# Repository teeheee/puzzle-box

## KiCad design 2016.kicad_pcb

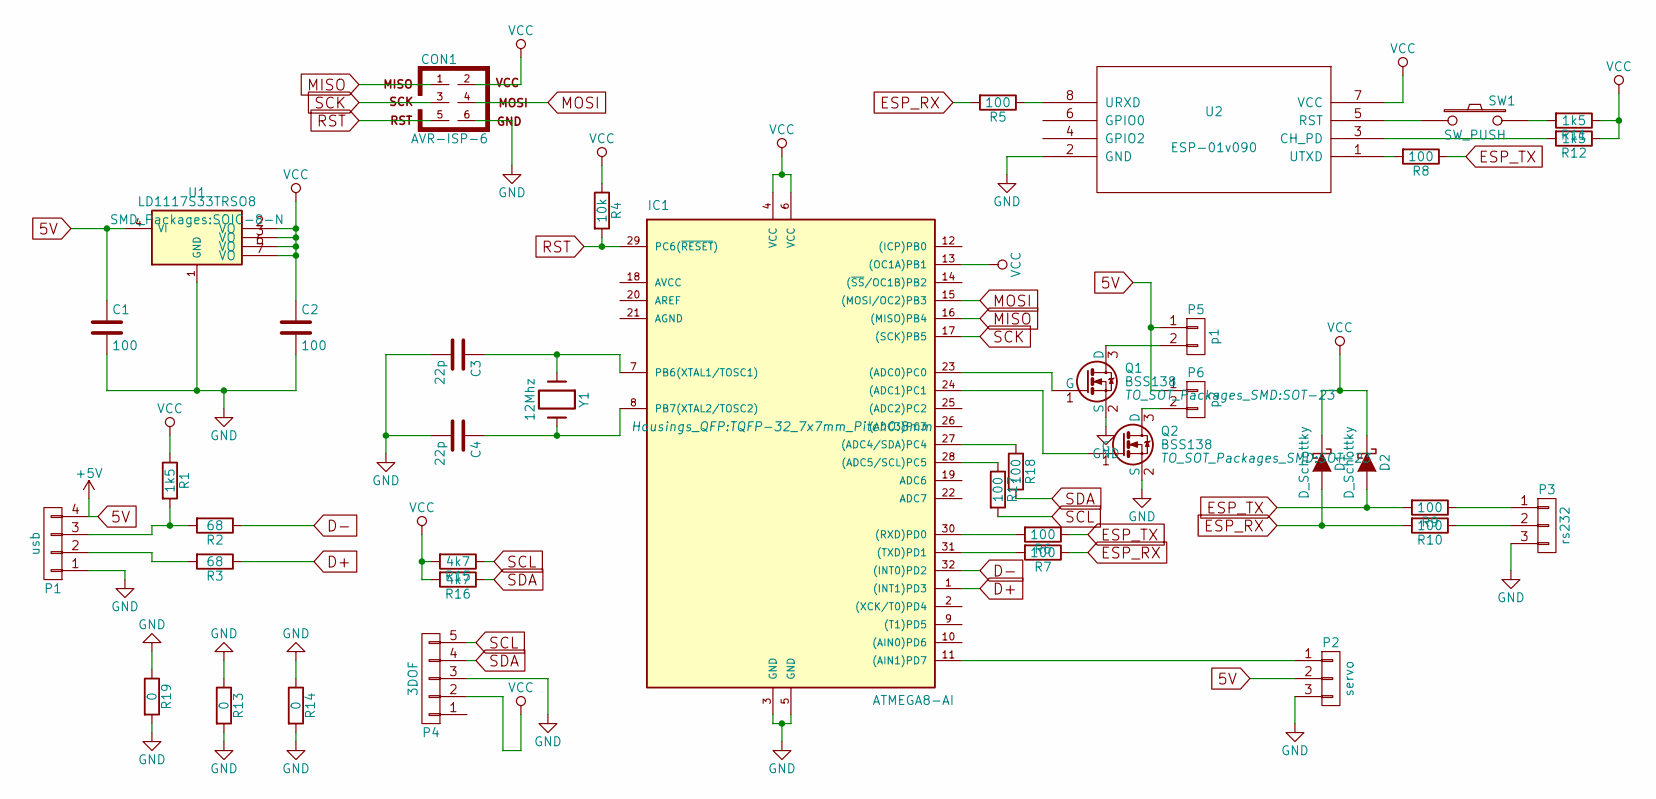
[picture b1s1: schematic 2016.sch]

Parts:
C1, C2: 100; C_0805_HandSoldering
C3, C4: 22p; C_0805_HandSoldering
CON1: AVR-ISP-6; Pin_Header_Straight_2x03
D1, D2: D_Schottky; C_1206_HandSoldering
IC1: ATMEGA8-AI; TQFP-32_7x7mm_Pitch0.8mm
P1: usb; Pin_Header_Straight_1x04
P2: servo; Pin_Header_Straight_1x03
P3: rs232; Pin_Header_Straight_1x03
P4: 3DOF; Socket_Strip_Straight_1x05
P5: p1; Pin_Header_Straight_1x02
P6: p2; Pin_Header_Straight_1x02
Q1, Q2: BSS138; SOT-23
R1, R11, R12: 1k5; R_0805_HandSoldering
R2, R3: 68; R_0805_HandSoldering
R4: 10k; R_0805_HandSoldering
R5, R6, R7, R8, R9, R10: 100; R_0805_HandSoldering
R13, R14, R19: 0; R_0805_HandSoldering
R15, R16: 4k7; R_0805_HandSoldering
R17, R18: 100; Resistor_Horizontal_RM7mm
SW1: SW_PUSH; SW_TH_Tactile_Omron_B3F-10xx
U1: LD1117S33TRSO8; SOIC-8-N
U2: ESP-01v090; ESP-01
Y1: 12Mhz; Crystal_HC49-U_Vertical

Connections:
5V: C1.1, P1.4, P2.2, P5.1, P6.1, U1.4 (VI)
D+: IC1.1 ((INT1)PD3), R3.1
D-: IC1.32 ((INT0)PD2), R2.1
ESP_RX: D1.2 (A), R5.2, R7.1, R10.2
ESP_TX: D2.2 (A), R6.1, R8.1, R9.2
GND: C1.2, C2.2, C3.2, C4.2, CON1.6, IC1.3 (GND), IC1.5 (GND), P1.1, P2.3, P3.3, P4.3, Q1.2 (S), Q2.2 (S), R13.1, R13.2, R14.1, R14.2, R19.1, R19.2, U1.1 (GND), U2.2 (GND)
MISO: CON1.1, IC1.16 ((MISO)PB4)
MOSI: CON1.4, IC1.15 ((MOSI/OC2)PB3)
unnamed: C3.1, IC1.7 (PB6(XTAL1/TOSC1)), Y1.1
unnamed: C4.1, IC1.8 (PB7(XTAL2/TOSC2)), Y1.2
unnamed: IC1.11 ((AIN1)PD7), P2.1
unnamed: IC1.23 ((ADC0)PC0), Q1.1 (G)
unnamed: IC1.24 ((ADC1)PC1), Q2.1 (G)
unnamed: IC1.27 ((ADC4/SDA)PC4), R18.1
unnamed: IC1.28 ((ADC5/SCL)PC5), R17.1
unnamed: IC1.30 ((RXD)PD0), R6.2
unnamed: IC1.31 ((TXD)PD1), R7.2
unnamed: P1.2, R3.2
unnamed: P1.3, R1.2, R2.2
unnamed: P3.1, R9.1
unnamed: P3.2, R10.1
unnamed: P5.2, Q1.3 (D)
unnamed: P6.2, Q2.3 (D)
unnamed: R5.1, U2.8 (URXD)
unnamed: R8.2, U2.1 (UTXD)
unnamed: R11.2, SW1.2
unnamed: R12.2, U2.3 (CH_PD)
unnamed: SW1.1, U2.5 (RST)
RST: CON1.5, IC1.29 (PC6(~RESET~)), R4.2
SCK: CON1.3, IC1.17 ((SCK)PB5)
SCL: P4.5, R15.1, R17.2
SDA: P4.4, R16.1, R18.2
VCC: C2.1, CON1.2, D1.1 (K), D2.1 (K), IC1.4 (VCC), IC1.6 (VCC), IC1.13 ((OC1A)PB1), P4.2, R1.1, R4.1, R11.1, R12.1, R15.2, R16.2, U1.2 (VO), U1.3 (VO), U1.6 (VO), U1.7 (VO), U2.7 (VCC)

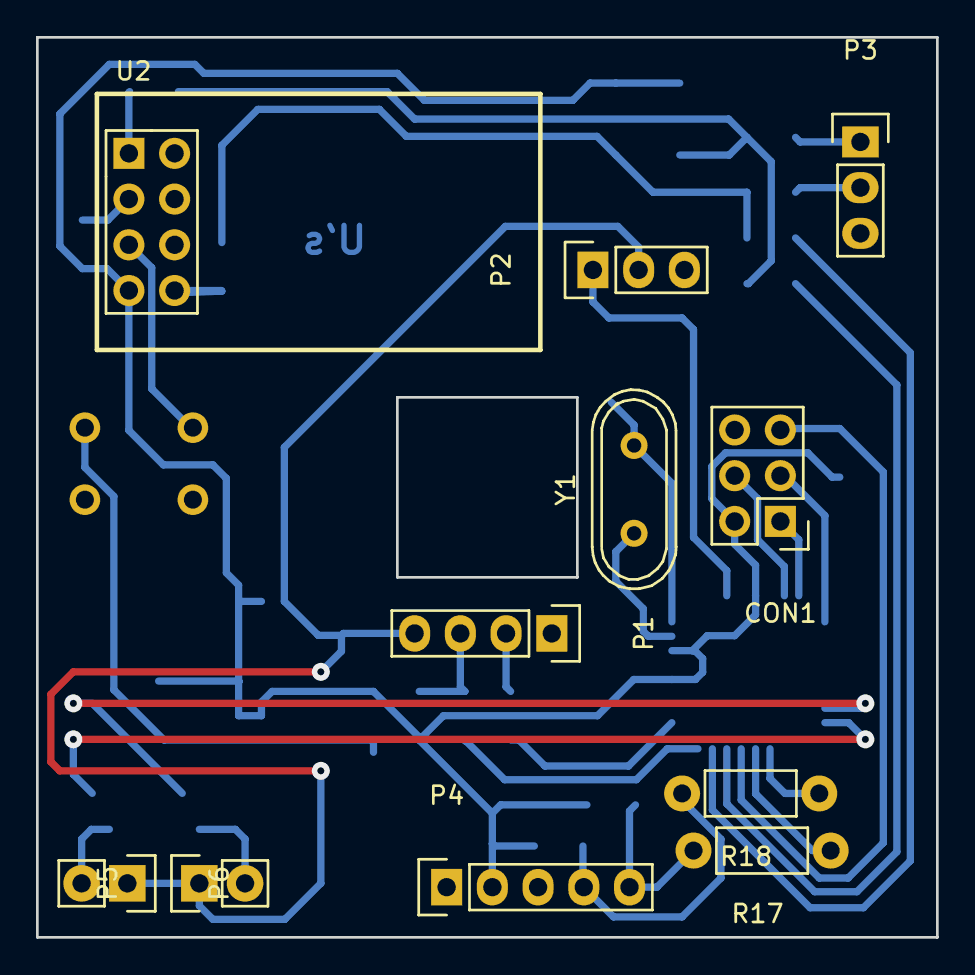
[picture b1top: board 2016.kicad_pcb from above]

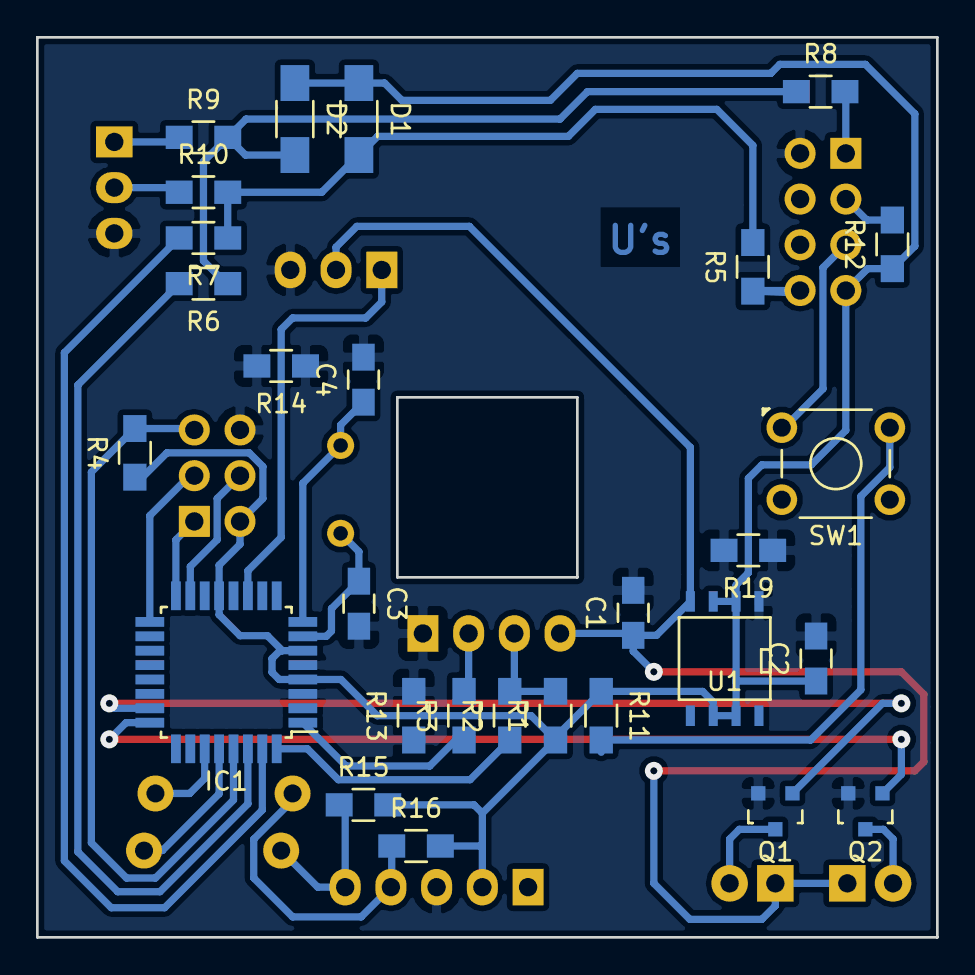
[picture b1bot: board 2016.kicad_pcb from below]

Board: 2 copper layers, 50.0 x 50.0 mm, 39 parts (28 on the bottom side), 33 nets.

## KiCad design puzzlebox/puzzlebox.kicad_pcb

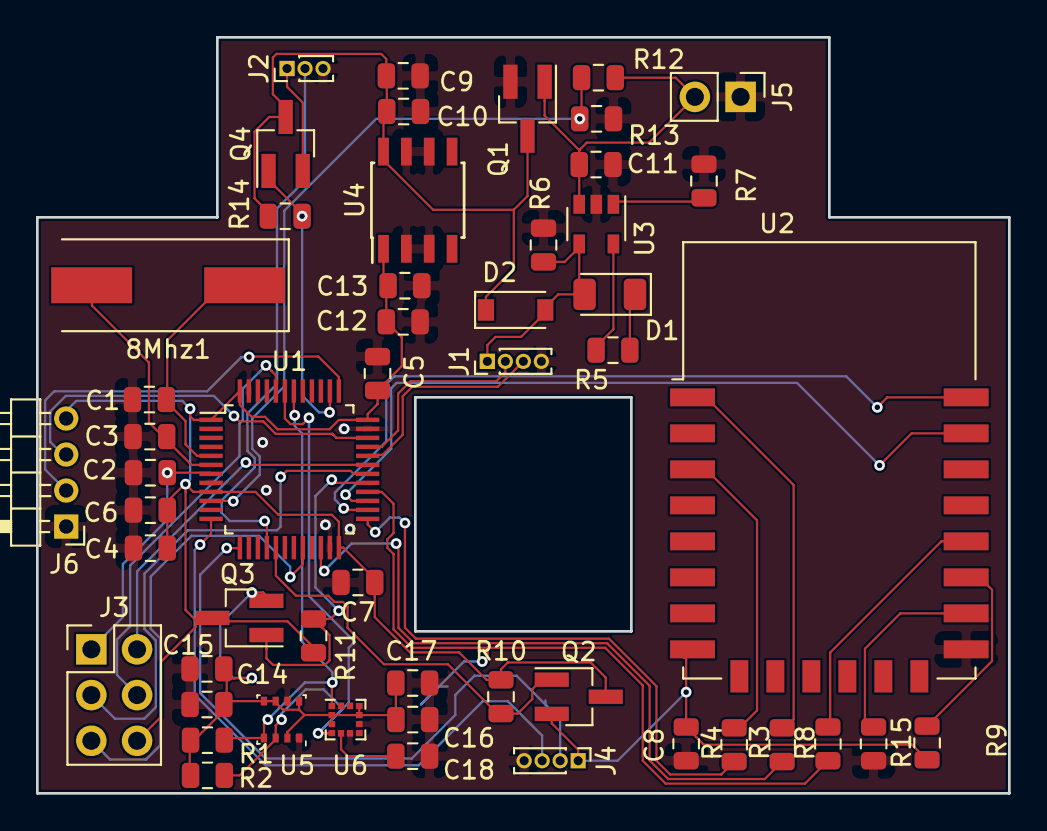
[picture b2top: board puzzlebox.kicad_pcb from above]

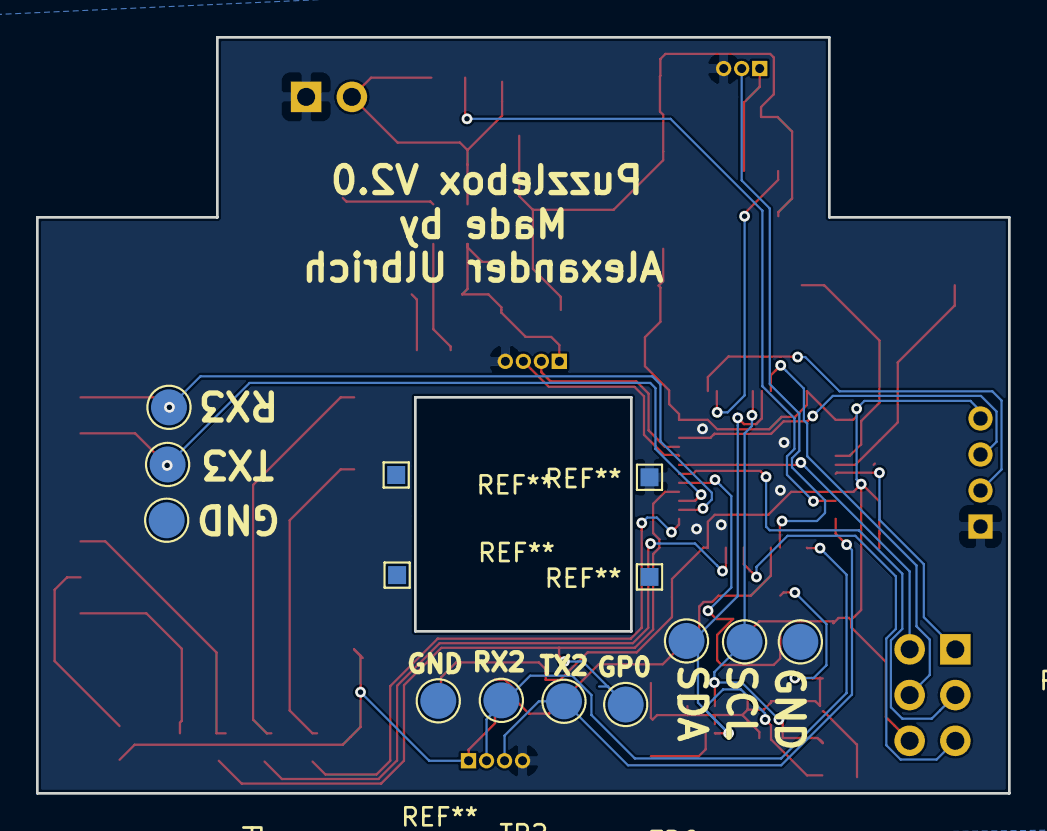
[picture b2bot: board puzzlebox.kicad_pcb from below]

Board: 2 copper layers, 54.0 x 42.0 mm, 59 parts (7 on the bottom side), 42 nets.

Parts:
8Mhz1: Crystal; Crystal_SMD_HC49-SD
C1, C3: 22p; C_0805_2012Metric
C2, C4, C5, C6, C7, C8, C10, C13, C14, C15, C16, C17, C18: 100n; C_0805_2012Metric
C9, C11, C12: 4u7; C_0805_2012Metric
D1: LED; LED_1206_3216Metric
D2: D; D_SOD-123
J1: USB; PinHeader_1x04_P1.00mm_Vertical
J2: Servo; PinHeader_1x03_P1.00mm_Vertical
J3: Conn_01x06_Male; PinHeader_2x03_P2.54mm_Vertical
J4: GPS; PinHeader_1x04_P1.00mm_Vertical
J5: Batt; PinHeader_1x02_P2.54mm_Vertical
J6: SWD; PinHeader_1x04_P2.00mm_Horizontal
Q1: Q_NMOS_DGS; BSS138
Q2, Q3, Q4: Q_PMOS_GSD; BSS138
R1, R2: 4k7; R_0805_2012Metric
R3, R4, R8, R15: 1k; R_0805_2012Metric
R5: 470; R_0805_2012Metric
R6, R9, R10, R11, R14: 10k; R_0805_2012Metric
R7: 2k; R_0805_2012Metric
R12, R13: 100k; R_0805_2012Metric
TP1, TP7: TX2; TestPoint_Pad_D2.0mm
TP2: RX2; TestPoint_Pad_D2.0mm
TP3: RX3; TestPoint_Pad_D2.0mm
TP4: TX3; TestPoint_Pad_D2.0mm
TP5: SCL1; TestPoint_Pad_D2.0mm
TP6: SDA1; TestPoint_Pad_D2.0mm
U1: STM32F103C8Tx; LQFP-48_7x7mm_P0.5mm
U2: ESP-12E
U3: MCP73831; SOT-23-5
U4: L78L33_SO8; SOIC-8_3.9x4.9mm_P1.27mm
U5: BME280; Bosch_LGA-8_2.5x2.5mm_P0.65mm_ClockwisePinNumbering
U6: LSM303C; LGA-12_2x2mm_P0.5mm

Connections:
BAT+: C11.1, J5.2, Q1.1, R12.2, U3.3
ENABLE1: Q3.1, R11.2, U1.29
ENABLE2: Q2.1, R10.2, U1.17
ENABLE3: Q4.1, R14.2, U1.38
GND: C1.1, C2.2, C3.1, C4.2, C5.2, C6.2, C7.2, C8.2, C9.2, C10.2, C11.2, C12.2, C13.2, C14.2, C15.2, C16.2, C17.2, C18.2, J1.4, J2.3, J4.4, J5.1, J6.1, Q1.2, R6.2, R7.2, R9.1, R13.1, U1.8, U1.23, U1.35, U1.47, U2.15, U3.2, U4.2, U4.3, U4.6, U4.7, U5.1, U5.7, U6.6, U6.8
NRST: C2.1, J3.1, U1.7
unnamed: 8Mhz1.1, C1.2, U1.5
unnamed: 8Mhz1.2, C3.2, U1.6
unnamed: C18.1, U6.5
unnamed: D1.1, R5.1
unnamed: J6.2, U1.37
unnamed: J6.3, U1.34
unnamed: R3.1, U2.1
unnamed: R4.1, U2.3
unnamed: R5.2, U3.5
unnamed: R7.1, U3.1
unnamed: R8.2, U2.18
unnamed: R9.2, U2.16
unnamed: R15.2, U2.17
SCL1: R1.2, TP5.1, U1.42, U5.4, U6.1
SDA1: R2.2, TP6.1, U1.43, U5.3, U6.4
SENS_BAT: R12.1, R13.2, U1.10
SERVO_PWM: J2.2, U1.16
USART1_RX: J3.2, U1.31
USART1_TX: J3.3, U1.30
USART2_RX: J4.2, TP2.1, U1.13
USART2_TX: J4.3, TP1.1, U1.12
USART3_RX: TP3.1, U1.26, U2.22
USART3_TX: TP4.1, U1.27, U2.21
USB+: D1.2, D2.2, J1.1, R6.1, U3.4
USB_N: J1.3, U1.32
USB_P: J1.2, U1.33
VCC: C4.1, C5.1, C6.1, C7.1, C12.1, C13.1, J3.6, J6.4, Q2.3, Q3.3, R10.1, R11.1, U1.1, U1.9, U1.24, U1.36, U1.48, U4.1
VCC_1: C14.1, C15.1, C16.1, C17.1, Q3.2, R1.1, R2.1, U5.2, U5.5, U5.6, U5.8, U6.2, U6.3, U6.9, U6.10
VCC_2: C8.1, J4.1, Q2.2, R15.1, U2.8
VSS: C9.1, C10.1, D2.1, Q1.3, Q4.3, R14.1, U4.8
VSS_1: J2.1, Q4.2
boot0: J3.4, U1.44
boot1: J3.5, U1.20
esp_enable: R4.2, U1.25
esp_flash: R8.1, TP7.1, U1.28
esp_reset: R3.2, U1.22

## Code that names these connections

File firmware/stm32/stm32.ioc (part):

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Mcu.Name=STM32F103C(4-6)Tx
Mcu.Package=LQFP48
Mcu.UserName=STM32F103C4Tx
PA0-WKUP.Signal=ADCx_IN0
PA10.Mode=Asynchronous
PA10.Signal=USART1_RX
PA13.Mode=Serial_Wire
PA13.Signal=SYS_JTMS-SWDIO
PA14.Mode=Serial_Wire
PA14.Signal=SYS_JTCK-SWCLK
PA2.Mode=Asynchronous
PA2.Signal=USART2_TX
PA3.Mode=Asynchronous
PA3.Signal=USART2_RX
PA6.Signal=GPIO_Output
PA7.Signal=GPIO_Output
PA8.Signal=GPIO_Output
PA9.Mode=Asynchronous
PA9.Signal=USART1_TX
PB11.Signal=GPIO_Output
PB12.Signal=GPIO_Output
PB15.Signal=GPIO_Output
PB6.Mode=I2C
PB6.Signal=I2C1_SCL
PB7.Mode=I2C
PB7.Signal=I2C1_SDA
board=custom

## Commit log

2019-11-03 finished V2.0 for production
2019-11-03 changed layoutname
2019-11-03 cleanup
2019-11-30 added stencils and made the first programm that flashs
2019-12-22 changed stm32 enviroment to cubemx
2019-12-22 stm32 first test version finished
    it can get open requests from esp8266 and open the lock with the servo.
